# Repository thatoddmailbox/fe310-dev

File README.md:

# fe310-dev

A development board for the [SiFive FE310](https://sifive.cdn.prismic.io/sifive/4999db8a-432f-45e4-bab2-57007eed0a43_fe310-g002-datasheet-v1p2.pdf), a RISC-V microcontroller. Compatible with both the FE310-G000 and FE310-G002.

## Revisions
* Revision 0 - initial revision
	* [revision 0 schematic](./mfg/rev0/fe310-dev.pdf), [revision 0 gerbers](./mfg/rev0), [revision 0 known issues](https://github.com/thatoddmailbox/fe310-dev/issues?q=is%3Aissue+label%3A%22affects+rev+0%22+) 
* Revision 1 - added support for the G002, added mounting holes, fixed silkscreen labels for pins and LEDs
	* [revision 1 schematic](./mfg/rev1/fe310-dev.pdf), [revision 1 gerbers](./mfg/rev1), [revision 1 known issues](https://github.com/thatoddmailbox/fe310-dev/issues?q=is%3Aissue+label%3A%22affects+rev+1%22+)

## Pinouts
The main pins are on the sides, and are labeled on the silkscreen. PWM capable pins are labeled with a ~, and pins with support for the SPI or UART peripherals have their functions labeled.

In the middle of the board, there are two sets of pins. The first is the JTAG header, which is partially labeled. When holding the board upright (so the "FE310 dev board" text can be read, and the USB port faces upwards), the pins are as follows:

* +3.3V
* TCK
* TDO
* TMS
* TDI
* GND

Most of these should go directly to the matching pin on your JTAG adapter. The one exception is +3.3V. If you want to power the board from your adapter, connect +3.3V to your adapter's power; however, if you want to power the board from USB (so that you can see the serial port), then leave the JTAG header's +3.3V pin disconnected.

The second set of pins has no labels. When holding the board upright, the pins are as follows:

* +1.8V
* AON_PMU_OUT_0
* AON_PMU_OUT_1
* AON_PMU_DWAKEUP_N
* AON_ERST_N
* AON_PSD_LFALTCLK
* AON_PSD_LFALTSEL
* GND

These are part of the Always-On (AON) Block of the FE310. You can check the FE310 manual for more information about these pins; however, in most cases, the only relevant pin is AON_ERST_N, which resets the chip (and is connected to the Reset button on the board). **Note that just because there's a +1.8V pin does _not_ mean the AON pins operate at 1.8V. See [issue #7](https://github.com/thatoddmailbox/fe310-dev/issues/7) for details.**

## Helpful links
* [Forked freedom-e-sdk](https://github.com/thatoddmailbox/freedom-e-sdk)
* [Revision 1 Schematic](./mfg/rev1/fe310-dev.pdf)
* [FE310-G002 Datasheet v1p0](https://sifive.cdn.prismic.io/sifive%2F3d777659-a0dd-49ed-a011-5bebba17aecf_fe310-g002-ds.pdf)
* [FE310-G002 Manual v19p04](https://sifive.cdn.prismic.io/sifive%2F9ecbb623-7c7f-4acc-966f-9bb10ecdb62e_fe310-g002.pdf)

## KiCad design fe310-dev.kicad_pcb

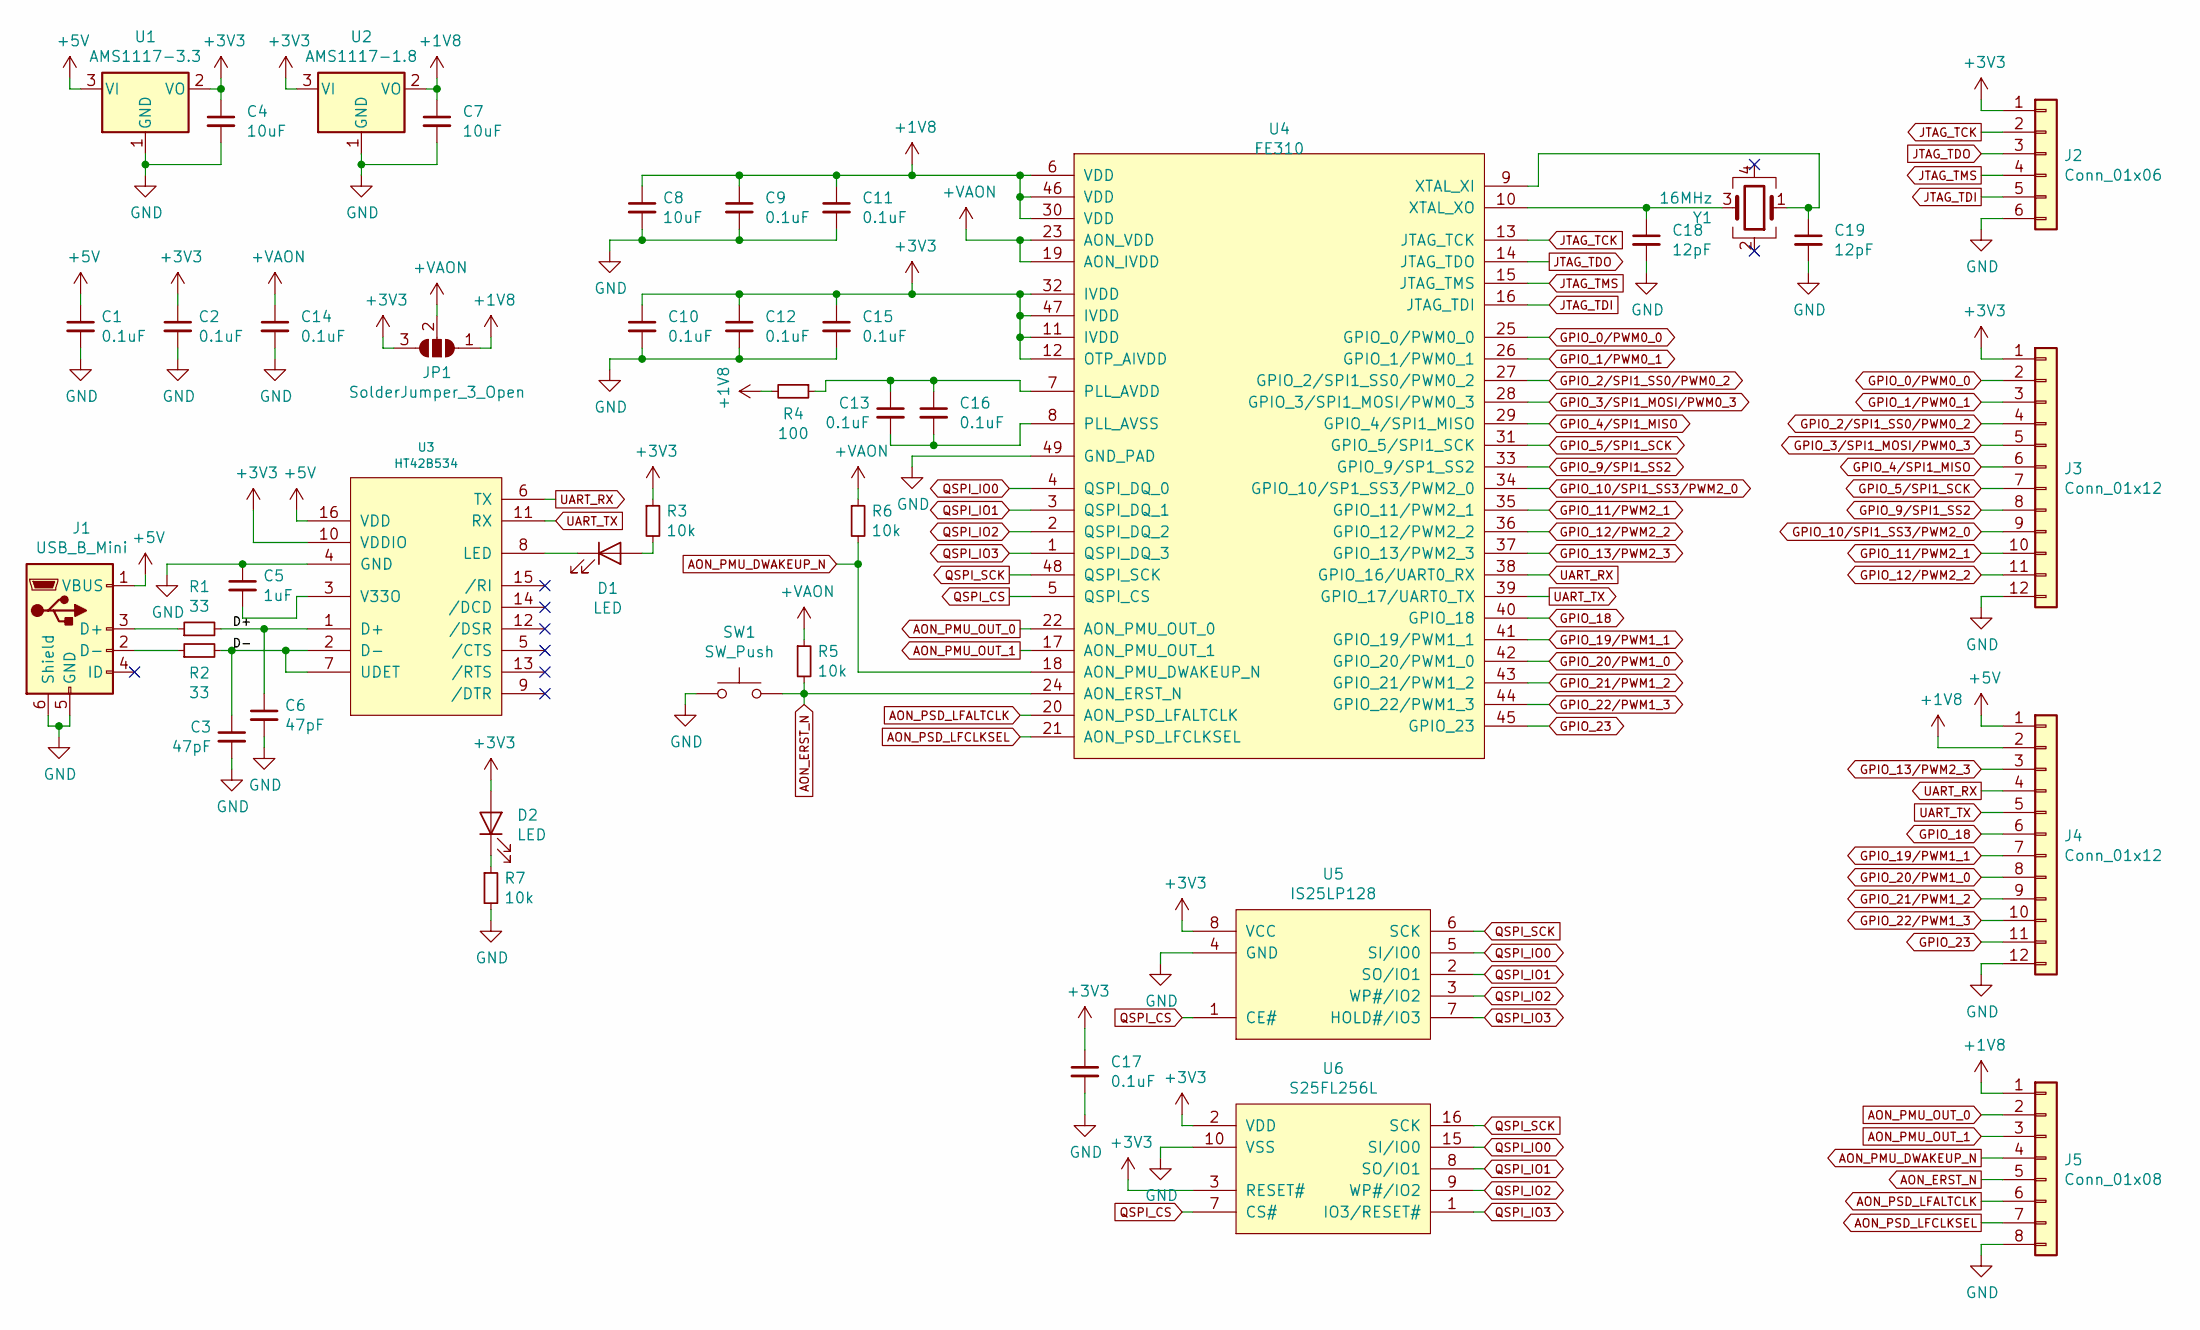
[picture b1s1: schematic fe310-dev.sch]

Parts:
C1, C2, C9, C10, C11, C12, C13, C14, C15, C16, C17: 0.1uF; C_0603_HandSoldering
C3, C6: 47pF; C_0603_HandSoldering
C4, C7, C8: 10uF; C_0603_HandSoldering
C5: 1uF; C_0603_HandSoldering
C18, C19: 12pF; C_0603_HandSoldering
D1, D2: LED; LED_0603_HandSoldering
J1: USB_B_Mini; USB_Mini-B
J2: Conn_01x06; Pin_Header_Straight_1x06_Pitch2.54mm
J3, J4: Conn_01x12; Pin_Header_Straight_1x12_Pitch2.54mm
J5: Conn_01x08; Pin_Header_Straight_1x08_Pitch2.54mm
JP1: SolderJumper_3_Open; SolderJumper-3_P1.3mm_Open_RoundedPad1.0x1.5mm
R1, R2: 33; R_0603_HandSoldering
R3, R5, R6, R7: 10k; R_0603_HandSoldering
R4: 100; R_0603_HandSoldering
SW1: SW_Push; SW_SPST_PTS645
U1: AMS1117-3.3; SOT-223-3_TabPin2
U2: AMS1117-1.8; SOT-223-3_TabPin2
U3: HT42B534; SOIC-16_3.9x9.9mm_Pitch1.27mm
U4: FE310; QFN-48-1EP_6x6mm_Pitch0.4mm_ThermalVias
U5: IS25LP128; SO-8_5.3x6.2mm_Pitch1.27mm
U6: S25FL256L; SOIC-16W_7.5x10.3mm_Pitch1.27mm
Y1: 16MHz; Crystal_SMD_3225-4pin_3.2x2.5mm_HandSoldering

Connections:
+1V8: C7.1, C8.1, C9.1, C11.1, J4.2, J5.1, JP1.1 (A), R4.2, U2.2 (VO), U4.6 (VDD), U4.30 (VDD), U4.46 (VDD)
+3V3: C2.1, C4.1, C10.1, C12.1, C15.1, C17.1, D2.2 (A), J2.1, J3.1, JP1.3 (B), R3.1, U1.2 (VO), U2.3 (VI), U3.10 (VDDIO), U4.11 (IVDD), U4.12 (OTP_AIVDD), U4.32 (IVDD), U4.47 (IVDD), U5.8 (VCC), U6.2 (VDD), U6.3 (RESET#)
+5V: C1.1, J1.1 (VBUS), J4.1, U1.3 (VI), U3.16 (VDD)
+VAON: C14.1, JP1.2 (C), R5.1, R6.1, U4.19 (AON_IVDD), U4.23 (AON_VDD)
/D+: C6.1, R1.2, U3.1 (D+)
/D-: C3.1, R2.2, U3.2 (D-), U3.7 (UDET)
AON_ERST_N: J5.5, R5.2, SW1.2, U4.24 (AON_ERST_N)
AON_PMU_DWAKEUP_N: J5.4, R6.2, U4.18 (AON_PMU_DWAKEUP_N)
AON_PMU_OUT_0: J5.2, U4.22 (AON_PMU_OUT_0)
AON_PMU_OUT_1: J5.3, U4.17 (AON_PMU_OUT_1)
AON_PSD_LFALTCLK: J5.6, U4.20 (AON_PSD_LFALTCLK)
AON_PSD_LFCLKSEL: J5.7, U4.21 (AON_PSD_LFCLKSEL)
GND: C1.2, C2.2, C3.2, C4.2, C5.1, C6.2, C7.2, C8.2, C9.2, C10.2, C11.2, C12.2, C14.2, C15.2, C17.2, C18.2, C19.2, J1.5 (GND), J1.6 (Shield), J2.6, J3.12, J4.12, J5.8, R7.2, SW1.1, U1.1 (GND), U2.1 (GND), U3.4 (GND), U4.49 (GND_PAD), U5.4 (GND), U6.10 (VSS)
GPIO_0/PWM0_0: J3.2, U4.25 (GPIO_0/PWM0_0)
GPIO_1/PWM0_1: J3.3, U4.26 (GPIO_1/PWM0_1)
GPIO_2/SPI1_SS0/PWM0_2: J3.4, U4.27 (GPIO_2/SPI1_SS0/PWM0_2)
GPIO_3/SPI1_MOSI/PWM0_3: J3.5, U4.28 (GPIO_3/SPI1_MOSI/PWM0_3)
GPIO_4/SPI1_MISO: J3.6, U4.29 (GPIO_4/SPI1_MISO)
GPIO_5/SPI1_SCK: J3.7, U4.31 (GPIO_5/SPI1_SCK)
GPIO_9/SPI1_SS2: J3.8, U4.33 (GPIO_9/SP1_SS2)
GPIO_10/SPI1_SS3/PWM2_0: J3.9, U4.34 (GPIO_10/SP1_SS3/PWM2_0)
GPIO_11/PWM2_1: J3.10, U4.35 (GPIO_11/PWM2_1)
GPIO_12/PWM2_2: J3.11, U4.36 (GPIO_12/PWM2_2)
GPIO_13/PWM2_3: J4.3, U4.37 (GPIO_13/PWM2_3)
GPIO_18: J4.6, U4.40 (GPIO_18)
GPIO_19/PWM1_1: J4.7, U4.41 (GPIO_19/PWM1_1)
GPIO_20/PWM1_0: J4.8, U4.42 (GPIO_20/PWM1_0)
GPIO_21/PWM1_2: J4.9, U4.43 (GPIO_21/PWM1_2)
GPIO_22/PWM1_3: J4.10, U4.44 (GPIO_22/PWM1_3)
GPIO_23: J4.11, U4.45 (GPIO_23)
JTAG_TCK: J2.2, U4.13 (JTAG_TCK)
JTAG_TDI: J2.5, U4.16 (JTAG_TDI)
JTAG_TDO: J2.3, U4.14 (JTAG_TDO)
JTAG_TMS: J2.4, U4.15 (JTAG_TMS)
unnamed: C5.2, U3.3 (V33O)
unnamed: C13.1, C16.1, R4.1, U4.7 (PLL_AVDD)
unnamed: C13.2, C16.2, U4.8 (PLL_AVSS)
unnamed: C18.1, U4.10 (XTAL_XO), Y1.3
unnamed: C19.1, U4.9 (XTAL_XI), Y1.1
unnamed: D1.1 (K), U3.8 (LED)
unnamed: D1.2 (A), R3.2
unnamed: D2.1 (K), R7.1
unnamed: J1.2 (D-), R2.1
unnamed: J1.3 (D+), R1.1
QSPI_CS: U4.5 (QSPI_CS), U5.1 (CE#), U6.7 (CS#)
QSPI_IO0: U4.4 (QSPI_DQ_0), U5.5 (SI/IO0), U6.15 (SI/IO0)
QSPI_IO1: U4.3 (QSPI_DQ_1), U5.2 (SO/IO1), U6.8 (SO/IO1)
QSPI_IO2: U4.2 (QSPI_DQ_2), U5.3 (WP#/IO2), U6.9 (WP#/IO2)
QSPI_IO3: U4.1 (QSPI_DQ_3), U5.7 (HOLD#/IO3), U6.1 (IO3/RESET#)
QSPI_SCK: U4.48 (QSPI_SCK), U5.6 (SCK), U6.16 (SCK)
UART_RX: J4.4, U3.6 (TX), U4.38 (GPIO_16/UART0_RX)
UART_TX: J4.5, U3.11 (RX), U4.39 (GPIO_17/UART0_TX)

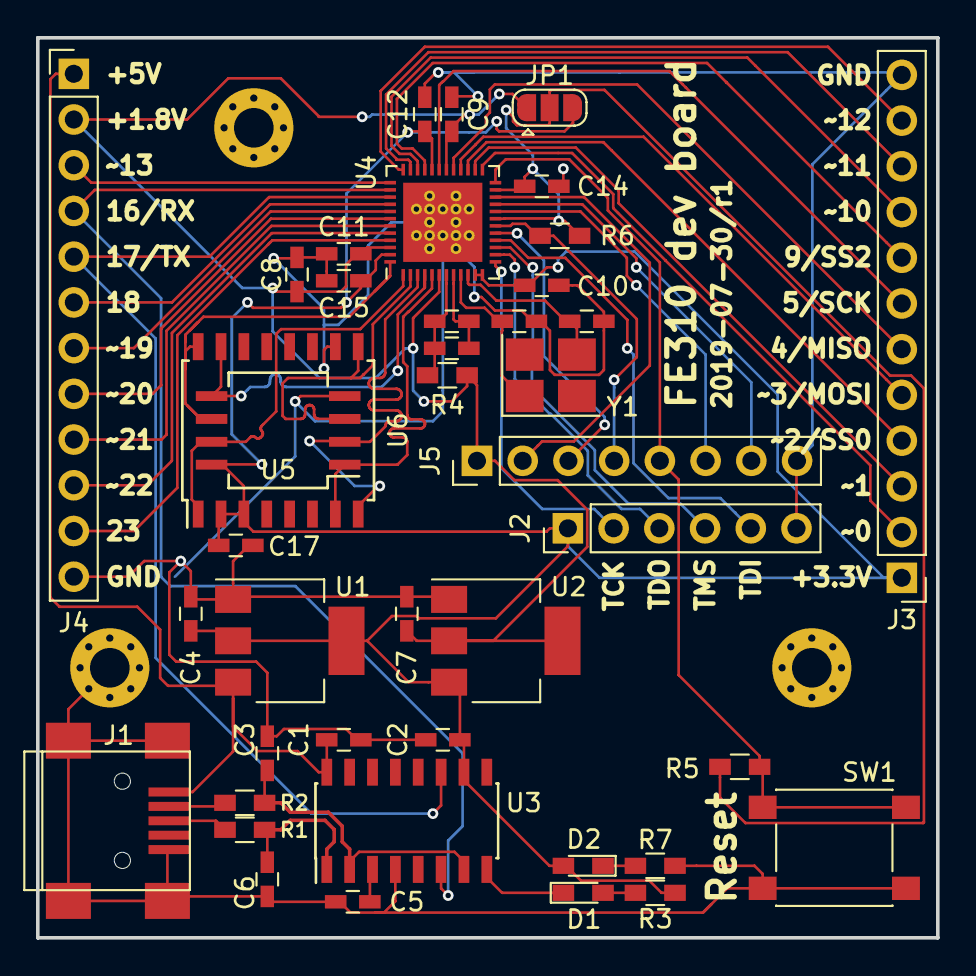
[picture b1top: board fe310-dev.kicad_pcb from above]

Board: 2 copper layers, 50.0 x 50.0 mm, 42 parts (0 on the bottom side), 52 nets.

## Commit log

2019-06-07 commit rev 0 schematic, pcb, and gerbers
2019-06-08 add a README and image
2019-07-04 use path substitution instead of absolute path to library
2019-07-04 add jumper for selectable AON power domain voltage, which should work for #5
2019-07-04 pullup for AON_ERST_N should be connected to the AON i/o voltage
2019-07-04 same for AON wakeup pin...
2019-07-05 various fixes and updates to silkscreen, closes #1 and #2
2019-07-05 add m2 mounting holes and reroute traces to accommodate (closes #3)
2019-07-30 update date on pcb because i'm lazy and took 3 weeks before sending the board to be fabbed
2019-07-30 add gerbers for rev 1
2021-01-24 tested with g002 and it works!
    close #5
2021-01-25 readme: add notes on revisions
2021-01-25 readme: add pinouts section
2021-01-25 readme: document the AON header
2021-01-25 readme: add note about reset pin
2021-01-25 readme: add links to datasheet and manual
2021-01-25 readme: add note about AON power domain
2021-01-25 readme: make issue reference a link
    i thought it would automatically link and it didn't >:(
2021-01-25 readme: add link to rev1 schematic
2021-01-25 readme: add link to forked freedom-e-sdk
2021-01-26 readme: add links to known issue labels
2021-01-26 update image to be rev 1
2021-01-26 readme: add clearer links to schematic and gerbers
2021-01-26 add gimp files to gitignore
2021-01-26 readme: add labeled version of main image
2021-01-26 update labeled image
2021-01-26 exclude jpg_original files from git
2021-01-26 update image labels
2021-01-26 add manufacturer name to label for HT42B534
2021-01-26 add LICENSE
2021-01-26 readme: small tweak to description
2021-01-26 readme: move known issue links
2021-12-29 readme: update fe310 link to a non-broken but not very useful one
    for some reason sifive has removed any actually useful pages on their site about the fe310
